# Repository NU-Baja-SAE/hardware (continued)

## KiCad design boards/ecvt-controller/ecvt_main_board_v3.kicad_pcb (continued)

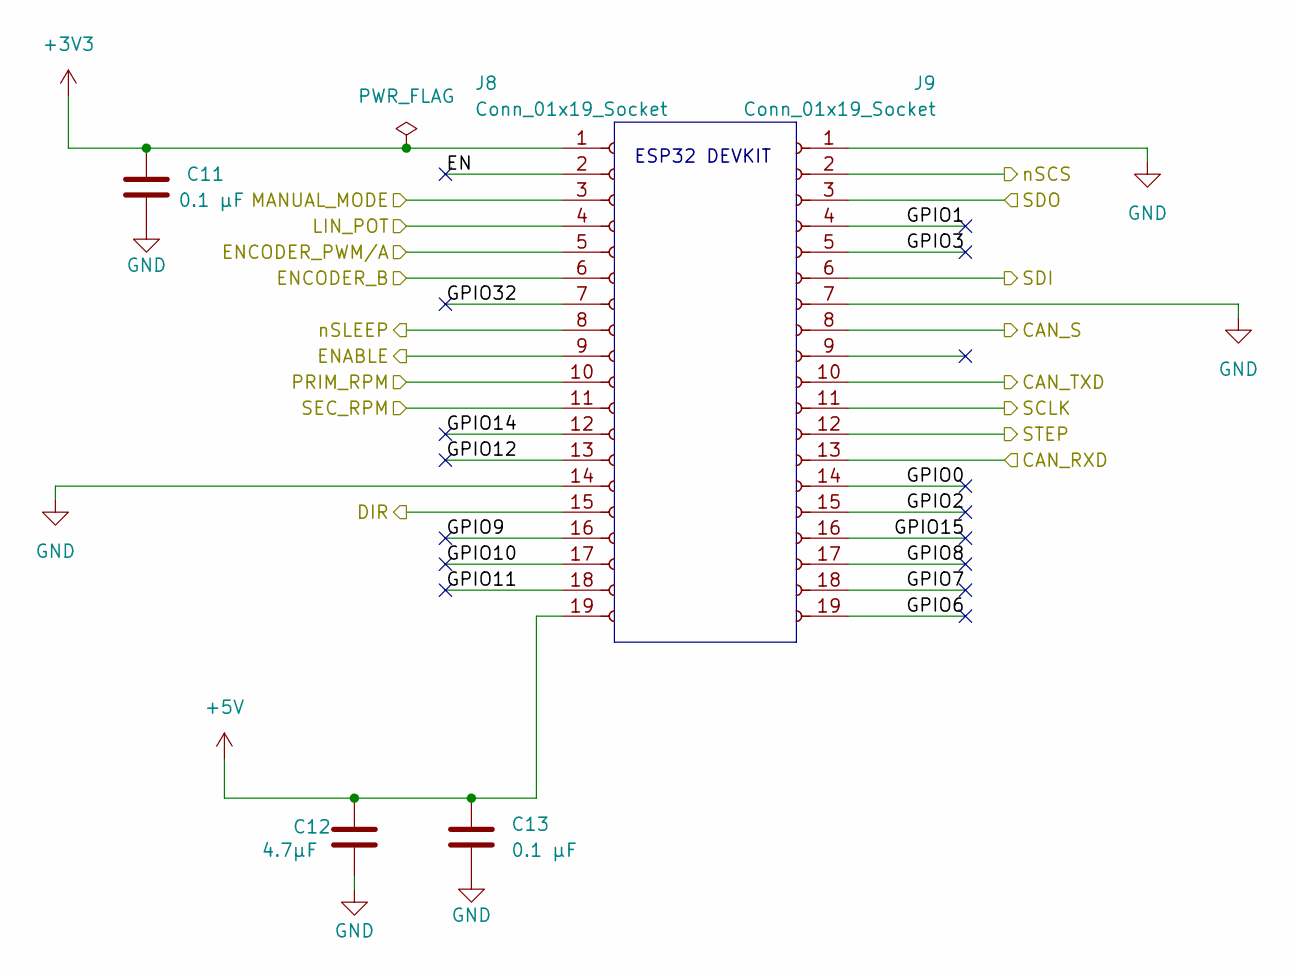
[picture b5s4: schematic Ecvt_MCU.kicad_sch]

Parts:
C11, C13: 0.1 µF; C_0603_1608Metric_Pad1.08x0.95mm_HandSolder
C12: 4.7µF; C_0603_1608Metric_Pad1.08x0.95mm_HandSolder
J8, J9: Conn_01x19_Socket; PinSocket_1x19_P2.54mm_Vertical

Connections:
+3V3: C11.1, J8.1; also elsewhere on the board
+5V: C12.1, C13.1, J8.19; also elsewhere on the board
/CAN Transceiver/RXD: J9.13; also elsewhere on the board
/CAN Transceiver/S: J9.8; also elsewhere on the board
/CAN Transceiver/TXD: J9.10; also elsewhere on the board
/Connector Bank/ENCODER_B: J8.6; also elsewhere on the board
/Connector Bank/ENCODER_PWM/A: J8.5; also elsewhere on the board
/Connector Bank/LIN_POT: J8.4; also elsewhere on the board
/Connector Bank/MANUAL_MODE: J8.3; also elsewhere on the board
/Connector Bank/PRIM_RPM: J8.10; also elsewhere on the board
/Connector Bank/SEC_RPM: J8.11; also elsewhere on the board
/Ecvt_MCU/DIR: J8.15; also elsewhere on the board
/Ecvt_MCU/EN: J8.2
/Ecvt_MCU/ENABLE: J8.9; also elsewhere on the board
/Ecvt_MCU/GPIO0: J9.14
/Ecvt_MCU/GPIO1: J9.4
/Ecvt_MCU/GPIO2: J9.15
/Ecvt_MCU/GPIO3: J9.5
/Ecvt_MCU/GPIO6: J9.19
/Ecvt_MCU/GPIO7: J9.18
/Ecvt_MCU/GPIO8: J9.17
/Ecvt_MCU/GPIO9: J8.16
/Ecvt_MCU/GPIO10: J8.17
/Ecvt_MCU/GPIO11: J8.18
/Ecvt_MCU/GPIO12: J8.13
/Ecvt_MCU/GPIO14: J8.12
/Ecvt_MCU/GPIO15: J9.16
/Ecvt_MCU/GPIO32: J8.7
/Ecvt_MCU/SCLK: J9.11; also elsewhere on the board
/Ecvt_MCU/SDI: J9.6; also elsewhere on the board
/Ecvt_MCU/SDO: J9.3; also elsewhere on the board
/Ecvt_MCU/STEP: J9.12; also elsewhere on the board
/Ecvt_MCU/nSCS: J9.2; also elsewhere on the board
/Ecvt_MCU/nSLEEP: J8.8; also elsewhere on the board
GND: C11.2, C12.2, C13.2, J8.14, J9.1, J9.7; also elsewhere on the board

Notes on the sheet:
ESP32 DEVKIT

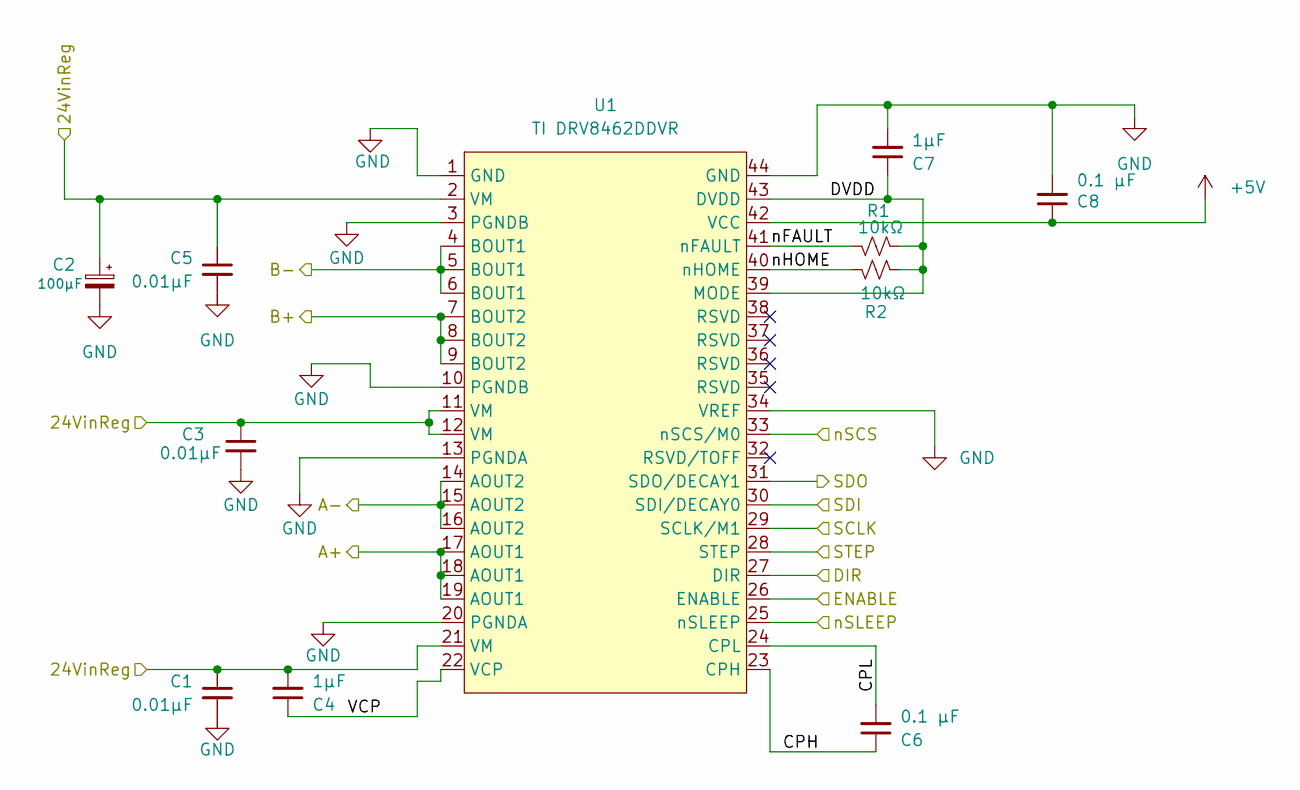
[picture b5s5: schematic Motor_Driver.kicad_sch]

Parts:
C1, C3, C5: 0.01µF; C_0603_1608Metric_Pad1.08x0.95mm_HandSolder
C2: 100µF; CP_Elec_10x10.5
C4, C7: 1µF; C_0603_1608Metric_Pad1.08x0.95mm_HandSolder
C6, C8: 0.1 µF; C_0603_1608Metric_Pad1.08x0.95mm_HandSolder
R1, R2: 10kΩ; R_0603_1608Metric_Pad0.98x0.95mm_HandSolder
U1: TI DRV8462DDVR; HTSSOP-44_6.1x14mm_P0.635mm_TopEP4.14x7.01mm

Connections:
+5V: C8.1, U1.42 (VCC); also elsewhere on the board
/Connector Bank/A+: U1.17 (AOUT1), U1.18 (AOUT1), U1.19 (AOUT1); also elsewhere on the board
/Connector Bank/A-: U1.14 (AOUT2), U1.15 (AOUT2), U1.16 (AOUT2); also elsewhere on the board
/Connector Bank/B+: U1.7 (BOUT2), U1.8 (BOUT2), U1.9 (BOUT2); also elsewhere on the board
/Connector Bank/B-: U1.4 (BOUT1), U1.5 (BOUT1), U1.6 (BOUT1); also elsewhere on the board
/Ecvt_MCU/DIR: U1.27 (DIR); also elsewhere on the board
/Ecvt_MCU/ENABLE: U1.26 (ENABLE); also elsewhere on the board
/Ecvt_MCU/SCLK: U1.29 (SCLK/M1); also elsewhere on the board
/Ecvt_MCU/SDI: U1.30 (SDI/DECAY0); also elsewhere on the board
/Ecvt_MCU/SDO: U1.31 (SDO/DECAY1); also elsewhere on the board
/Ecvt_MCU/STEP: U1.28 (STEP); also elsewhere on the board
/Ecvt_MCU/nSCS: U1.33 (nSCS/M0); also elsewhere on the board
/Ecvt_MCU/nSLEEP: U1.25 (nSLEEP); also elsewhere on the board
/Motor Driver/24VinReg: C1.1, C2.1, C3.1, C4.2, C5.1, U1.2 (VM), U1.11 (VM), U1.12 (VM), U1.21 (VM); also elsewhere on the board
/Motor Driver/CPH: C6.1, U1.23 (CPH)
/Motor Driver/CPL: C6.2, U1.24 (CPL)
/Motor Driver/DVDD: C7.1, R1.2, R2.2, U1.39 (MODE), U1.43 (DVDD)
/Motor Driver/VCP: C4.1, U1.22 (VCP)
/Motor Driver/nFAULT: R1.1, U1.41 (nFAULT)
/Motor Driver/nHOME: R2.1, U1.40 (nHOME)
GND: C1.2, C2.2, C3.2, C5.2, C7.2, C8.2, U1.1 (GND), U1.3 (PGNDB), U1.10 (PGNDB), U1.13 (PGNDA), U1.20 (PGNDA), U1.34 (VREF), U1.44 (GND); also elsewhere on the board

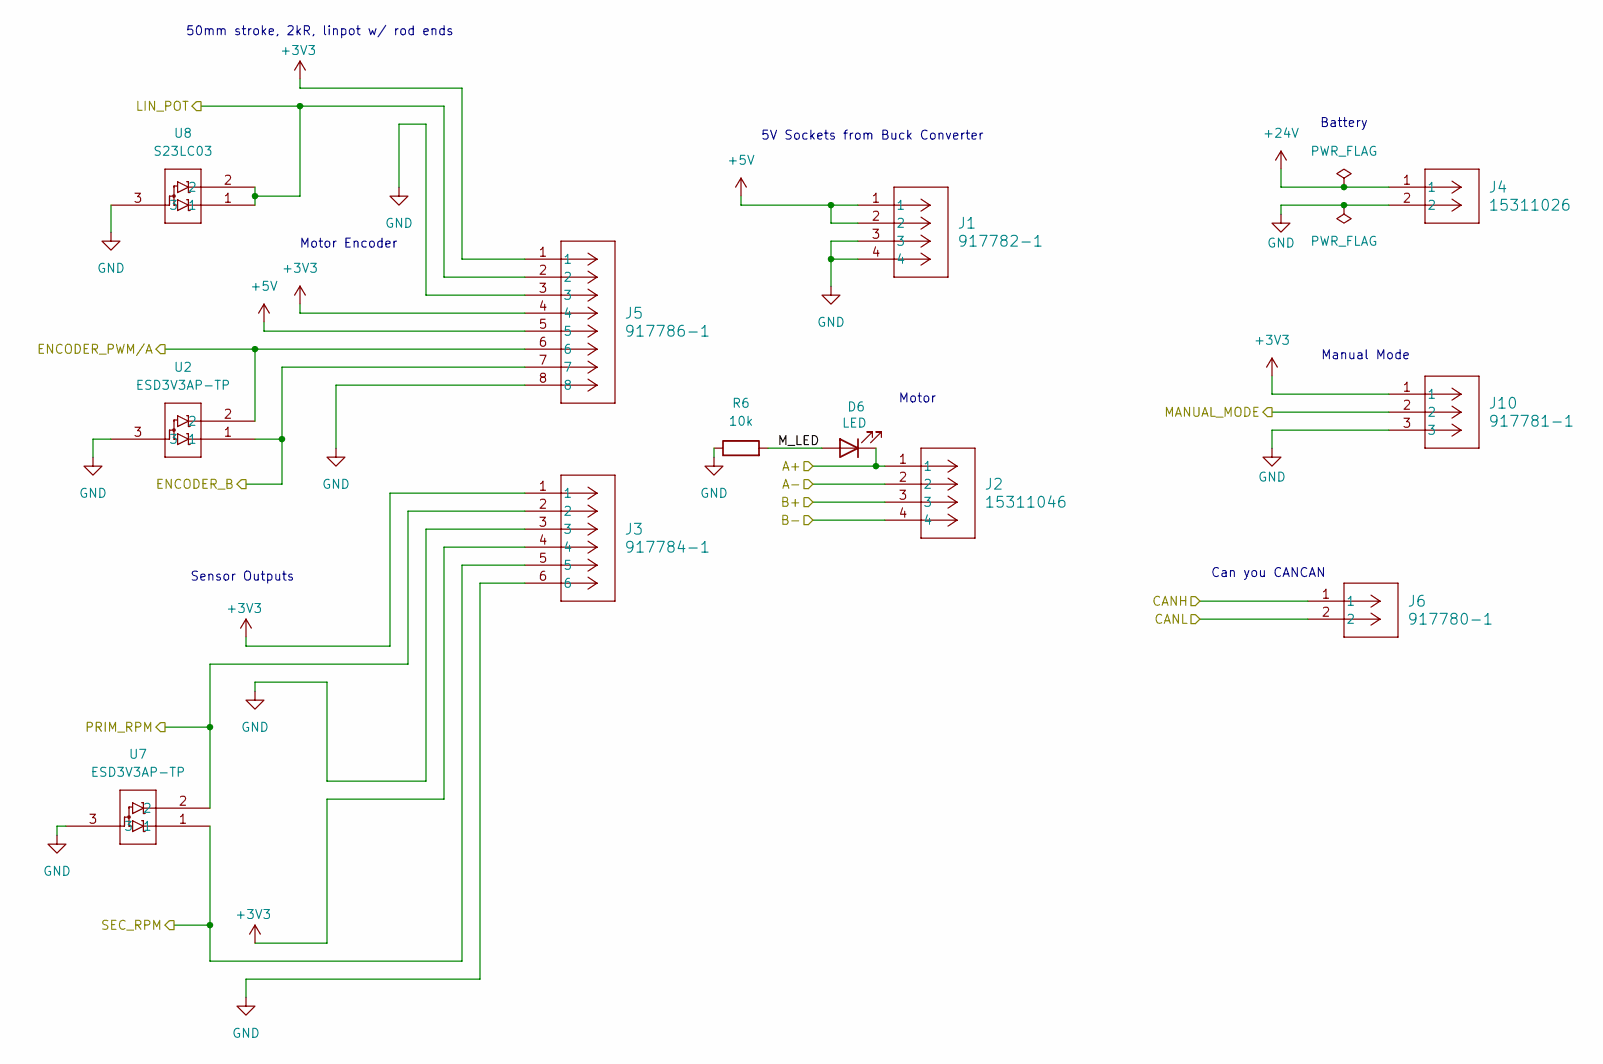
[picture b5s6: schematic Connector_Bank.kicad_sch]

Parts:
D6: LED; LED_Luminus_MP-3030-1100_3.0x3.0mm
J1: 917782-1; TE-Connectivity_917782
J2: 15311046; MOLEX_15311046
J3: 917784-1; TE-Connectivity_1x6
J4: 15311026; MOLEX_15311026
J5: 917786-1; TE-Connectivity_917786
J6: 917780-1; TE-Connectivity_ 917780
J10: 917781-1; TE-Connectivity_917781
R6: 10k; R_0603_1608Metric_Pad0.98x0.95mm_HandSolder
U2, U7: ESD3V3AP-TP; SOT-23
U8: S23LC03; SOT-23

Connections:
+3V3: J3.1, J3.4, J5.1, J5.4, J10.1; also elsewhere on the board
+5V: J1.1, J1.2, J5.5; also elsewhere on the board
+24V: J4.1; also elsewhere on the board
/CAN Transceiver/CANH: J6.1; also elsewhere on the board
/CAN Transceiver/CANL: J6.2; also elsewhere on the board
/Connector Bank/A+: D6.1 (K), J2.1; also elsewhere on the board
/Connector Bank/A-: J2.2; also elsewhere on the board
/Connector Bank/B+: J2.3; also elsewhere on the board
/Connector Bank/B-: J2.4; also elsewhere on the board
/Connector Bank/ENCODER_B: J5.7, U2.1; also elsewhere on the board
/Connector Bank/ENCODER_PWM/A: J5.6, U2.2; also elsewhere on the board
/Connector Bank/LIN_POT: J5.2, U8.1, U8.2; also elsewhere on the board
/Connector Bank/MANUAL_MODE: J10.2; also elsewhere on the board
/Connector Bank/M_LED: D6.2 (A), R6.2
/Connector Bank/PRIM_RPM: J3.2, U7.2; also elsewhere on the board
/Connector Bank/SEC_RPM: J3.5, U7.1; also elsewhere on the board
GND: J1.3, J1.4, J3.3, J3.6, J4.2, J5.3, J5.8, J10.3, R6.1, U2.3, U7.3, U8.3; also elsewhere on the board

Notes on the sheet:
5V Sockets from Buck Converter
Manual Mode
Motor
50mm stroke, 2kR, linpot w/ rod ends
Motor Encoder
Battery
Sensor Outputs
Can you CANCAN

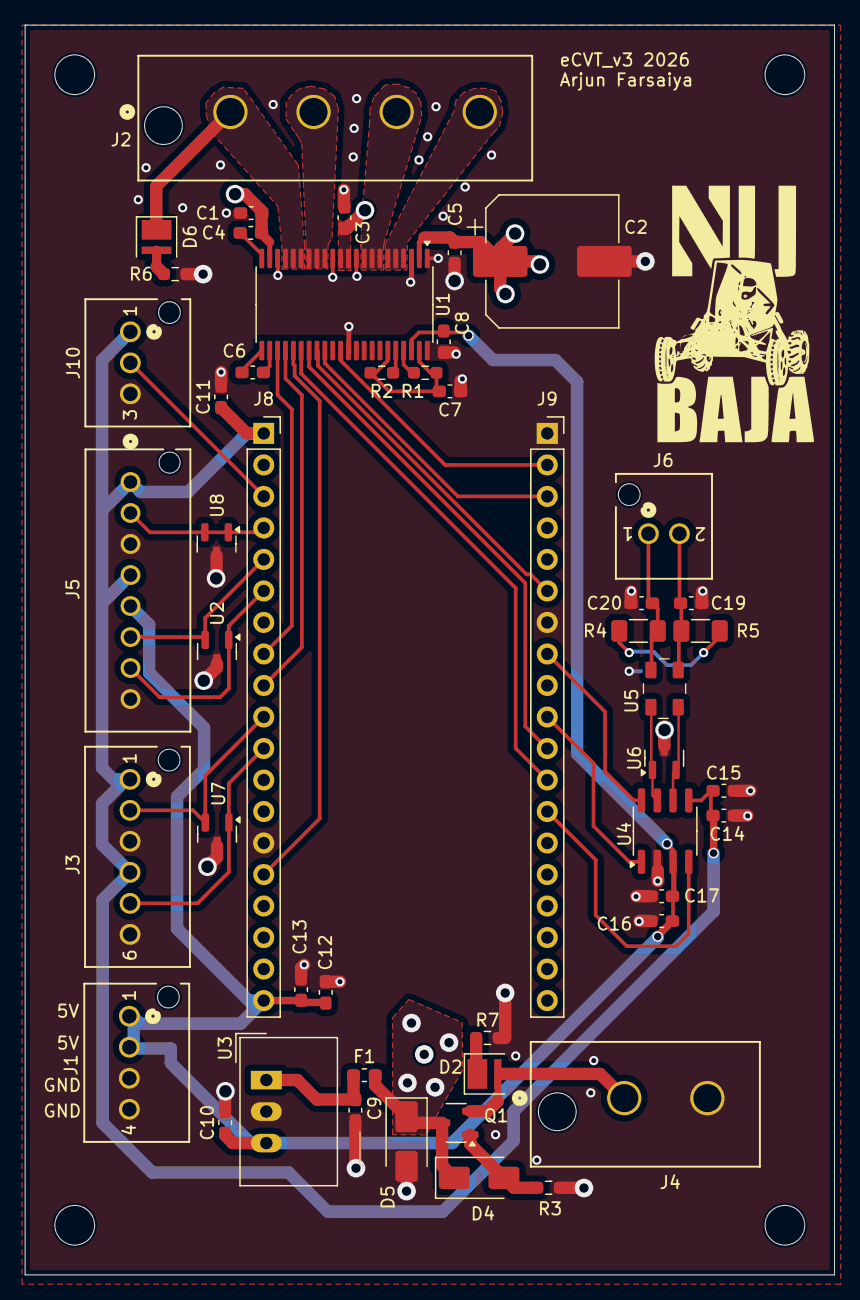
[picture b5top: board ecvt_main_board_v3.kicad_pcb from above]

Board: 4 copper layers, 65.2 x 100.8 mm, 54 parts (1 on the bottom side), 41 nets.

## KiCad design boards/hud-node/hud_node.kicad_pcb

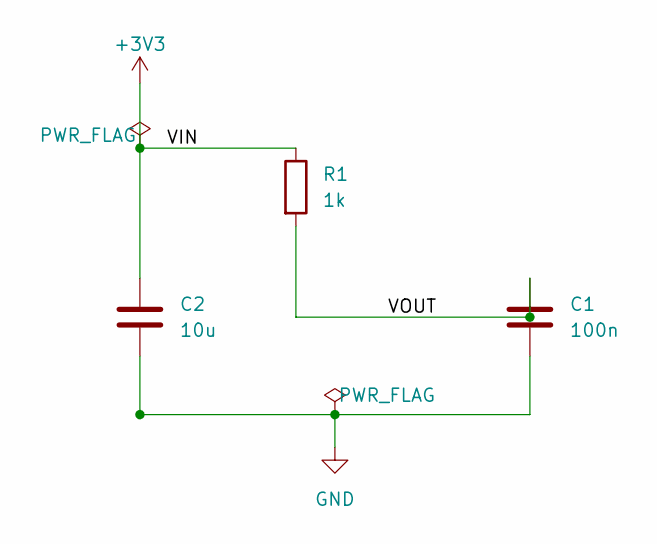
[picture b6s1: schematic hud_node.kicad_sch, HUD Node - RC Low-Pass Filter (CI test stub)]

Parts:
C1: 100n; C_0603_1608Metric_Pad1.08x0.95mm_HandSolder
C2: 10u; C_0805_2012Metric_Pad1.18x1.45mm_HandSolder
R1: 1k; R_0603_1608Metric_Pad0.98x0.95mm_HandSolder

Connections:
+3V3: C2.1, R1.1
GND: C1.2, C2.2
VOUT: C1.1, R1.2

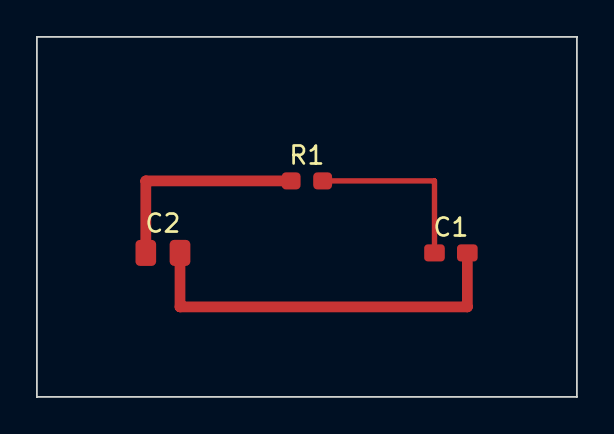
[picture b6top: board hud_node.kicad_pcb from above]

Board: 2 copper layers, 30.0 x 20.0 mm, 3 parts (0 on the bottom side), 3 nets.

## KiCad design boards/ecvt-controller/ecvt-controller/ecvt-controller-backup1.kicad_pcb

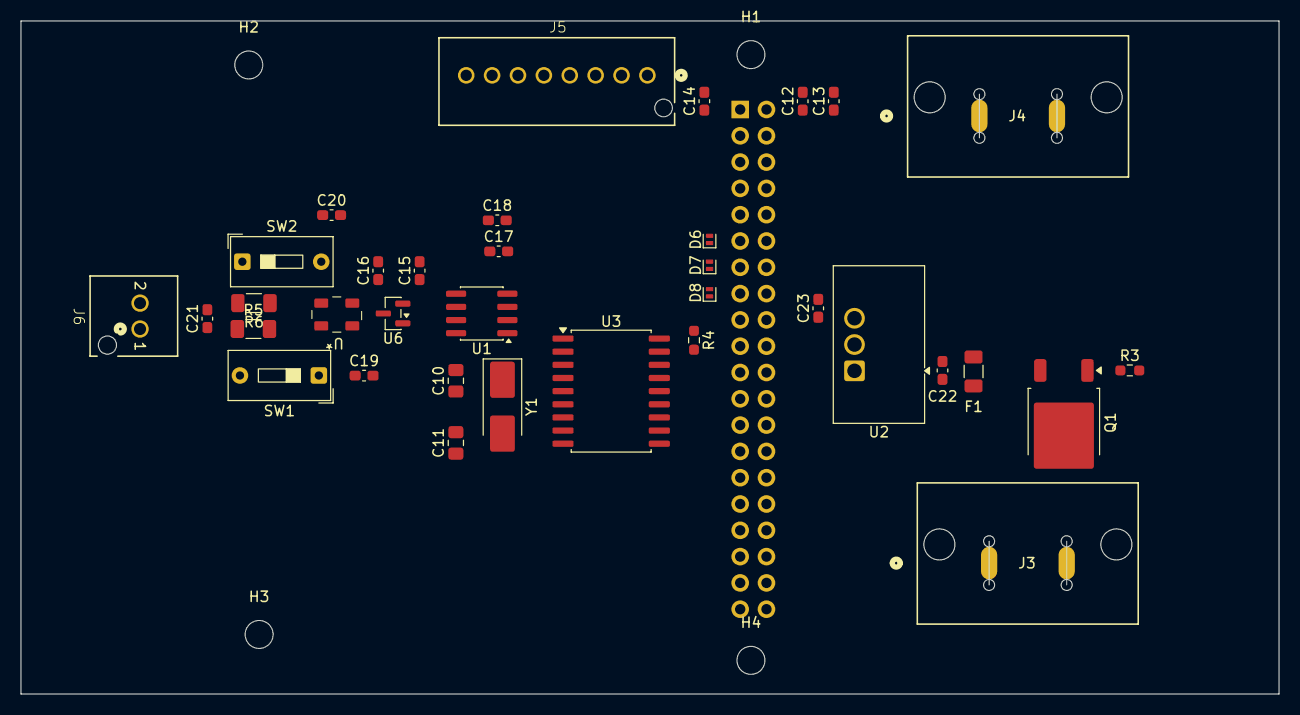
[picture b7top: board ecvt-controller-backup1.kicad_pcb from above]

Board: 2 copper layers, 121.5 x 65.0 mm, 40 parts (1 on the bottom side), 25 nets, no tracks yet.

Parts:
C10, C11: 22pF; C_0805_2012Metric_Pad1.18x1.45mm_HandSolder
C12, C15, C17: 4.7µF; C_0603_1608Metric_Pad1.08x0.95mm_HandSolder
C13, C14, C16, C18, C21, C22, C23: 0.1 µF; C_0603_1608Metric_Pad1.08x0.95mm_HandSolder
C19, C20: 220 pF; C_0603_1608Metric_Pad1.08x0.95mm_HandSolder
D6, D7, D8: DF2S5M4CTL3FCT-ND; D_SOD-882
F1: Fuse; Fuse_1206_3216Metric
H1, H2, H3, H4: MountingHole; MountingHole_2.7mm_M2.5
J1: Conn_02x20_Odd_Even; PinSocket_2x20_P2.54mm_Vertical
J3, J4: 1720420206; CONN_SD-172042-001_02_BL_MOL
J5: 917786-1; TE-Connectivity_917786
J6: 917780-1; TE-Connectivity_ 917780
Q1: Q_PMOS; TO-252-2
R3: 1k; R_0603_1608Metric_Pad0.98x0.95mm_HandSolder
R4: 10k; R_0603_1608Metric_Pad0.98x0.95mm_HandSolder
R5, R6: 60; R_1206_3216Metric_Pad1.30x1.75mm_HandSolder
SW1, SW2: SW_SPST; SW_DIP_SPSTx01_Slide_9.78x4.72mm_W7.62mm_P2.54mm
U1: TJA1051T-3; SOIC-8_3.9x4.9mm_P1.27mm
U2: TSR3-2450N; Converter_DCDC_TRACO_TSR2-24xxN_TSR2-24xxxN_THT
U3: MCP2515-xSO; SOIC-18W_7.5x11.6mm_P1.27mm
U5: ACT45B-101-2P-TL003
U6: PESD2CAN,215; SOT-23
Y1: Crystal; Crystal_SMD_5032-2Pin_5.0x3.2mm_HandSoldering

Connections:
+3.3V: C14.1, C15.1, C16.1, J1.1, J1.17, J5.1, J5.4, R4.1, U1.5 (VIO), U3.18 (VDD)
+5V: C12.1, C13.1, C17.1, C18.1, C23.1, J1.2, J1.4, U1.3 (VCC), U2.3 (Vout)
/CAN/CANH: C20.1, J6.1, SW1.1 (A), U5.4 (OUT1)
/CAN/CANL: C19.1, J6.2, SW2.2 (B), U5.3 (OUT2)
/Connectors/12V_Motor_Driver: F1.1, J4.1
/MCU/GPIO5: J1.29, U3.12 (~INT)
/MCU/GPIO8: J1.24, U3.16 (~CS)
/MCU/GPIO9: J1.21, U3.15 (SO)
/MCU/GPIO10: J1.19, U3.14 (SI)
/MCU/GPIO11: J1.23, U3.13 (SCK)
/MCU/GPIO17: D6.1 (K), J1.11, J5.2
/MCU/GPIO22: D8.1 (K), J1.15, J5.8
/MCU/GPIO27: D7.1 (K), J1.13, J5.5
GND: C10.1, C11.1, C12.2, C13.2, C14.2, C15.2, C16.2, C17.2, C18.2, C19.2, C20.2, C21.1, C22.2, C23.2, D6.2 (A), D7.2 (A), D8.2 (A), J1.6, J1.9, J1.14, J1.20, J1.25, J1.30, J1.34, J1.39, J3.2, J4.2, J5.3, J5.6, J5.7, R3.2, U1.2 (GND), U1.8 (S), U2.2 (GND), U3.9 (VSS), U6.3
unnamed: C21.2, R5.1, R6.2
unnamed: R5.2, SW1.2 (B)
unnamed: R6.1, SW2.1 (A)
unnamed: U1.7 (CANH), U5.1 (IN1), U6.1
unnamed: U1.6 (CANL), U5.2 (IN2), U6.2
unnamed: U1.4 (RXD), U3.2 (RXCAN)
unnamed: U1.1 (TXD), U3.1 (TXCAN)
unnamed: C22.1, F1.2, U2.1 (Vin)
unnamed: C11.2, U3.8 (OSC1), Y1.2
unnamed: C10.2, U3.7 (OSC2), Y1.1
unnamed: R4.2, U3.17 (~RESET)

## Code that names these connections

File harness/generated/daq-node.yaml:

# GENERATED by harness/scripts/extract_connectors.py -- DO NOT EDIT.
# Off-board harness connectors extracted from board 'daq-node'.
# Edit the board schematic and regenerate; never hand-edit this file.

metadata:
  name: daq-node off-board connectors

components:
  J10:
    type: connector
    label: daq-node J10 (917783-1)
    zone: daq-node
    pins:
      - {n: 1, name: GND}
      - {n: 2, name: GPIO39}
      - {n: 3, name: GPIO34}
      - {n: 4, name: GPIO35}
      - {n: 5, name: +5V}

  J13:
    type: connector
    label: daq-node J13 (917781-1)
    zone: daq-node
    pins:
      - {n: 1, name: GND}
      - {n: 2, name: GPIO36}
      - {n: 3, name: +5V}

  J15:
    type: connector
    label: daq-node J15 (917781-1)
    zone: daq-node
    pins:
      - {n: 1, name: +5V}
      - {n: 2, name: GPIO16}
      - {n: 3, name: GND}

  J2:
    type: connector
    label: daq-node J2 (917780-1)
    zone: daq-node
    pins:
      - {n: 1, name: CANH}
      - {n: 2, name: CANL}

  J3:
    type: connector
    label: daq-node J3 (917781-1)
    zone: daq-node
    pins:
      - {n: 1, name: GND}
      - {n: 2, name: Wheel 1}
      - {n: 3, name: +3.3V}

  J4:
    type: connector
    label: daq-node J4 (917781-1)
    zone: daq-node
    pins:
      - {n: 1, name: GND}
      - {n: 2, name: Fuel Sensor}
      - {n: 3, name: +5V}

  J5:
    type: connector
    label: daq-node J5 (917781-1)
    zone: daq-node
    pins:
      - {n: 1, name: GND}
      - {n: 2, name: Wheel 2}
      - {n: 3, name: +3.3V}

  J6:
    type: connector
    label: daq-node J6 (917780-1)
    zone: daq-node
    pins:
      - {n: 1, name: +12V}
      - {n: 2, name: GND}

  J7:
    type: connector
    label: daq-node J7 (917781-1)
    zone: daq-node
    pins:
      - {n: 1, name: GND}
      - {n: 2, name: SUS1}
      - {n: 3, name: +5V}

  J8:
    type: connector
    label: daq-node J8 (917781-1)
    zone: daq-node
    pins:
      - {n: 1, name: +5V}
      - {n: 2, name: GPIO17}
      - {n: 3, name: GND}

  J9:
    type: connector
    label: daq-node J9 (917781-1)
    zone: daq-node
    pins:
      - {n: 1, name: +5V}
      - {n: 2, name: GPIO21}
      - {n: 3, name: GND}

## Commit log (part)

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2026-06-30 Scaffold hardware monorepo structure
2026-06-30 Fix CI yaml line endings, drop telemetry-node (3 boards only)
2026-06-30 Normalize line endings to LF
2026-06-30 Remove comments from CI workflow that broke YAML parsing
2026-06-30 Quote run command values to fix YAML colon-in-plain-scalar parse error
